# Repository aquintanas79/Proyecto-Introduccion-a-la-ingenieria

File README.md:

# CHALECO HÁPTICO
Proyecto de Introduccion y Taller de ingeniería electrónica - UNAL - 2025-2

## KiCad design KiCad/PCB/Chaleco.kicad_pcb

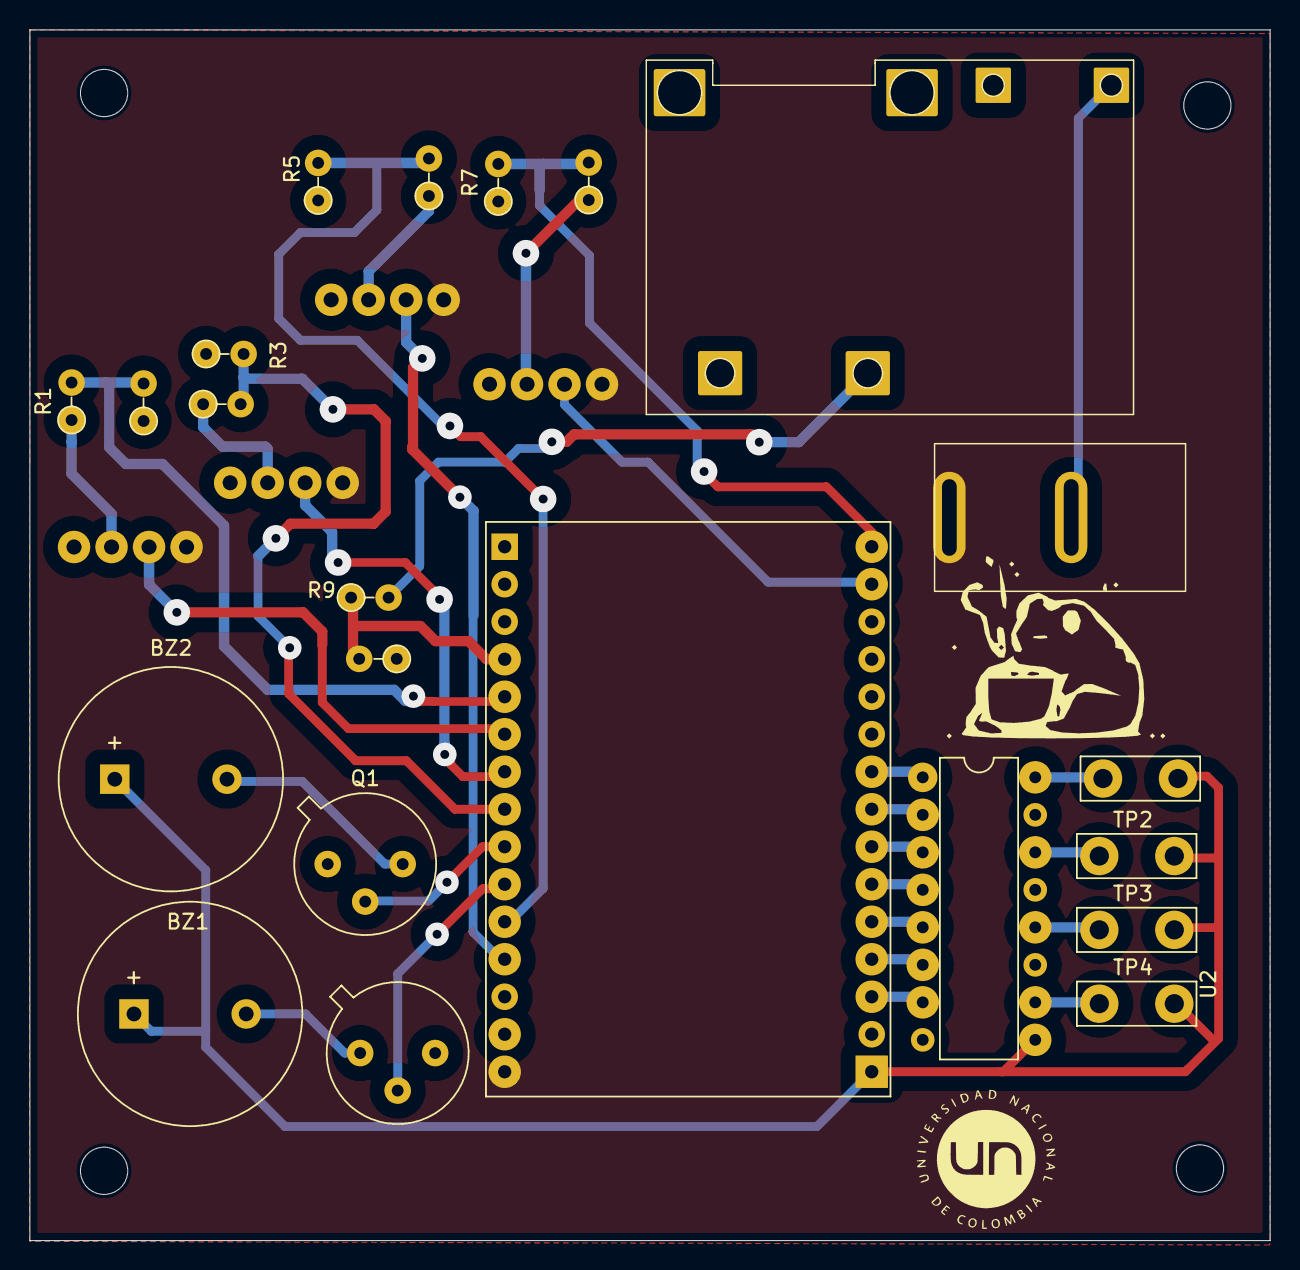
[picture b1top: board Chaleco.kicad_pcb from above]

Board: 2 copper layers, 84.0 x 82.0 mm, 26 parts (0 on the bottom side), 33 nets.

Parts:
BZ1, BZ2: Buzzer; Buzzer_15x7.5RM7.6
Q1: Q_NPN_EBC; TO-39-3
Q4: NPN; TO-39-3
R1, R4, R6, R8: 10 Kohm; R_Axial_DIN0204_L3.6mm_D1.6mm_P2.54mm_Vertical
R2, R3, R5, R7: 15Kohm; R_Axial_DIN0204_L3.6mm_D1.6mm_P2.54mm_Vertical
R9, R10: 100 Kohm; R_Axial_DIN0204_L3.6mm_D1.6mm_P2.54mm_Vertical
SW2: SW_DPST_x2; SWITCH
TP1, TP2, TP3, TP4: TestPoint_2Pole; TestPoint_Bridge_Pitch5.08mm_Drill1.3mm
U2: ULN2003A; DIP-16_W7.62mm
U3, U4, U5, U6: HC-SR04; XCVR_HC-SR04
U7: DEVKIT_V1_ESP32-WROOM-32; MODULE_DEVKIT_V1_ESP32-WROOM-32
U8: CARGADOR

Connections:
+3.3V: BZ1.1 (+), BZ2.1 (+), TP1.1, TP2.1, TP3.1, TP4.1, U2.9 (COM), U7.16
+5V: SW2.1 (A), U3.1 (VCC), U4.1 (VCC), U5.1 (VCC), U6.1 (VCC), U7.15 (VIN)
+BATT: R9.2, U8.1 (BAT_+)
/buzzer1: Q4.2 (B), U7.10 (IO27)
/buzzer2: Q1.2 (B), U7.9 (IO26)
/vout_bat_adc: R9.1, R10.2, U7.4 (IO34)
ECHO1: R1.2, R2.2, U7.5 (IO35)
ECHO2: R3.2, R4.2, U7.8 (IO25)
ECHO3: R5.2, R6.2, U7.11 (IO14)
ECHO4: R7.2, R8.2, U7.30 (IO17)
GND: Q1.1 (E), Q4.3 (E), R2.1, R3.1, R5.1, R7.1, R10.1, U2.8 (GND), U3.4 (GND), U4.4 (GND), U5.4 (GND), U6.4 (GND), U7.14 (GND1), U8.2 (BAT_)
unnamed: BZ1.2 (-), Q4.1 (C)
unnamed: BZ2.2 (-), Q1.3 (C)
unnamed: U2.1 (I1), U7.24 (3V3)
unnamed: U2.2 (I2), U7.23
unnamed: U2.3 (I3), U7.22
unnamed: U2.4 (I4), U7.21
unnamed: U2.5 (I5), U7.20
unnamed: U2.6 (I6), U7.19
unnamed: U2.7 (I7), U7.18
unnamed: TP1.1, U2.16 (O1)
unnamed: TP2.1, U2.14 (O3)
unnamed: TP3.1, U2.12 (O5)
unnamed: TP4.1, U2.10 (O7)
unnamed: R4.1, U3.3 (ECHO)
unnamed: R1.1, U4.3 (ECHO)
unnamed: R6.1, U5.3 (ECHO)
unnamed: R8.1, U6.3 (ECHO)
TRIG1: U4.2 (TRIG), U7.6 (IO32)
TRIG2: U3.2 (TRIG), U7.7 (IO33)
TRIG3: U5.2 (TRIG), U7.12 (IO12)
TRIG4: U6.2 (TRIG), U7.29 (IO16)
Vout_+: SW2.2 (B), U8.6 (Vout_)

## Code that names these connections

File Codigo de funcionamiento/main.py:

from machine import Pin, time_pulse_us, PWM, ADC
import time

NAME1 = "SENSOR 1"
TRIG1 = Pin(23, Pin.OUT)   # Pin TRIG1
ECHO1 = Pin(22, Pin.IN)    # Pin ECHO1
MOTOR1 = PWM(Pin(18), freq=1000) #pin Motor1

NAME2 = "SENSOR 2"
TRIG2 = Pin(12, Pin.OUT)   # Pin TRIG2
ECHO2 = Pin(14, Pin.IN)    # Pin ECHO2
MOTOR2 = PWM(Pin(5), freq=1000) #pin Motor2

NAME3 = "SENSOR 3"
TRIG3 = Pin(33, Pin.OUT)   # Pin TRIG3
ECHO3 = Pin(25, Pin.IN)    # Pin ECHO3
MOTOR3 = PWM(Pin(17), freq=1000) #pin

NAME4 = "SENSOR 4"
TRIG4 = Pin(32, Pin.OUT)   # Pin TRIG
ECHO4 = Pin(35, Pin.IN)    # Pin ECHO
MOTOR4 = PWM(Pin(16), freq=1000) #pin Motor4

# Pin ADC donde conectaste el divisor de voltaje
adc = ADC(Pin(34))
adc.atten(ADC.ATTN_11DB)   # Permite leer hasta ~3.3V
adc.width(ADC.WIDTH_12BIT) # Lectura de 0 a 4095

# Valores de tu divisor de voltaje
R1 = 100000   
R2 = 100000   

# --- Configuración del buzzer ---
buzzer = Pin(26, Pin.OUT)   
buzzer.value(0)

buzzer = Pin(27, Pin.OUT)   

# --- Al encender el ESP32, sonar el buzzer ---
buzzer.value(1)     
time.sleep(1)        
buzzer.value(0)

def medir_distancia(TRIG, ECHO):
    # Asegurar TRIG en bajo
    TRIG.value(0)
    time.sleep_us(5)

    # Pulso de 10us al TRIG
    TRIG.value(1)
    time.sleep_us(10)
    TRIG.value(0)

    # Medir duración del pulso en ECHO
    duracion = time_pulse_us(ECHO, 1, 80000)  # timeout 30ms

    if duracion < 0:
        return None  # No hubo lectura

    # Convertir a distancia (cm)
    distancia = (duracion * 0.0343) / 2
    return distancia

def vibrar(motor, distancia, name):
    if distancia is None:
        print(name + " No se detectó objeto.")
        print(name + " Motor apagado")
        motor.duty(0)
    else:
        print(name + " Distancia:", round(distancia, 2), "cm")
        if distancia < 100 and distancia >=50 :
            print(name + " Motor encendido leve")
            motor.duty(200)  # fuerza alta (0–1023)
        elif distancia < 50 and distancia >= 30:
            print(name + " Motor encendido suave")
            motor.duty(400)  # fuerza media
        elif distancia < 30 and distancia > 0:
            print(name + " Motor encendido fuerte")
            motor.duty(800)
        else:
            print(name + " Motor apagado")
            motor.duty(0)
            
def leer_bateria():
    lectura = adc.read()
    volt_esp = (lectura / 4095   ) * 3.3
    volt_bat = volt_esp * ((R1 + R2) / R2)
    print(lectura)
    return volt_bat


def porcentaje_bateria(v):
    if v >= 3.7: return 100
    if v <= 3.30: return 0
    return (v - 3.30) * 100 / (3.7 - 3.30)


def activar_buzzer():
    # Sonido corto
    buzzer.value(1)
    time.sleep(0.2)
    buzzer.value(0)
    time.sleep(0.2)

while True:
    distancia1 = medir_distancia(TRIG1, ECHO1)
    Zumbador1 = vibrar(MOTOR1, distancia1, NAME1)
    
    distancia2 = medir_distancia(TRIG2, ECHO2)
    Zumbador2 = vibrar(MOTOR2, distancia2, NAME2)
    
    distancia3 = medir_distancia(TRIG3, ECHO3)
    Zumbador3 = vibrar(MOTOR3, distancia3, NAME3)
    
    distancia4 = medir_distancia(TRIG4, ECHO4)
    Zumbador4 = vibrar(MOTOR4, distancia4, NAME4)
    
    while True:
        v = leer_bateria()
        p = porcentaje_bateria(v)
        print("Voltaje batería: {:.2f} V   |   Nivel: {:.0f}%".format(v, p))
        # Activar buzzer si batería está baja
        if p < 20:
            activar_buzzer()
        else:
            buzzer.value(0)
        time.sleep(1)

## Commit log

2025-11-09 Rename FLujoCHALECO (3).jpg to Diagrama_DeFLujo
2025-11-09 Proceso de Diseño
2025-11-09 Diagrama de Flujo
2025-11-09 Create Diagrama de Flujo
2025-11-09 Rename CAJANEGRA.jpg to Diagrama_CajaNegra.jpg
2025-11-09 Rename Diagrama de Flujo to Diagrama_Flujo
2025-11-09 Rename Diagrama_Flujo to Diagrama_Flujo.jpg
2025-11-09 Rename Diagrama_Flujo.jpg to try.jpg
2025-11-09 Rename FLujoCHALECO (3).jpg to Diagrama_Flujo.jpg
2025-11-09 Rename try.jpg to try
2025-11-09 Create cronograma
2025-11-09 Rename Informe#3 (3).pdf to Tercer informe de avance.pdf
2025-11-09 Rename 2do Avance (1).pdf to Segundo informe de avance.pdf
2025-11-09 Create x
2025-11-09 Create a
2025-11-09 Add files via upload
    DataSheet Buzzer activo TMB12A05
2025-11-09 Update x
2025-11-09 Rename x to conexion
2025-11-09 Rename ESP32-WROOM-32D.PDF to ESP32-WROOM-32U- Datasheet.PDF
2025-11-09 Rename nodemcu-esp32-pinout.png to esp32-pinout.png
2025-11-09 Rename HC-SR04.PDF to HC-SR04- Datasheet.PDF
2025-11-09 Rename doc-breadboard-wiring-hc-sr04-2-pins-esp32-schematic.webp to esquematico - esp32
2025-11-09 Rename esquematico - esp32 to esquematico - esp32.webp
2025-11-12 Rename 910-101-10mm-brushless-vibration-motor-3mm-type-datasheet.pdf to datasheet motores
2025-11-12 Rename datasheet motores to datasheet motores.webp
2025-11-12 Rename datasheet motores.webp to datasheet motores.pdf
2025-11-19 Rename WhatsApp Image 2025-11-19 at 11.59.23 AM.jpeg to Diagrama Tecnologico
2025-11-19 Rename Diagrama Tecnologico to Diagrama Tecnologico.jpg
2025-11-19 Rename Diagrama Tecnologico.jpg to Diagrama Kicad.jpg
2025-11-19 Rename WhatsApp Image 2025-11-19 at 12.08.13 PM.jpeg to Diagrama Kicad
2025-11-19 Rename Diagrama Kicad to Diagrama Kicad.jpg
2025-11-20 Rename WhatsApp Image 2025-11-20 at 10.34.14.jpeg to Diagrama de Kicad.jpg
2025-11-27 Create KiCad
2025-11-27 Add files via upload
    Avances de la pcb
